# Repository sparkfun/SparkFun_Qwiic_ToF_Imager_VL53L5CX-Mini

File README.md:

SparkFun Qwiic ToF Imager with VL53L5CX
========================================

[*SparkFun Qwiic Mini ToF Imager - VL53L5CX (SEN-19013)*](https://www.sparkfun.com/products/19013)

The SparkFun Qwiic Mini ToF Imager is a state of the art, 64 pixel Time-of-Flight (ToF) 4 meter ranging sensor built around the VL53L5CX from ST. This _Mini_ version has a footprint that is half the size (0.5 in x 1 in) of our standard [Qwiic VL53L5CX](https://www.sparkfun.com/products/18642). Additionally, we moved the Qwiic connectors to the back of the board in a vertical orientation. These design changes favor mounting applications where the VL53L5CX sensor faces outward from an enclosure or chassis, and keeps your Qwiic cables cleanly tucked away.  

This chip integrates a SPAD array, physical infrared filters, and diffractive optical elements (DOE) to achieve the best ranging performance in various ambient lighting conditions with a range of cover glass materials. Utilizing our handy Qwiic system, no soldering is required to connect it to the rest of your system. However, we still have broken out **some** 0.1"-spaced pins in case you prefer to use a breadboard.

Multizone distance measurements up to 4000mm are possible across all 64 zones with a wide 63° diagonal field-of-view which can be read up to 15Hz. Thanks to ST Histogram patented algorithms, the VL53L5CX is able to detect different objects within the FoV. The Histogram also provides immunity to cover glass crosstalk beyond 60 cm.

Ideal for 3D room mapping, obstacle detection for robotics, gesture recognition, IoT, laser-assisted autofocus, and AR/VR enhancement, the Qwiic connector on this sensor makes integration easy. 

SparkFun labored with love to create this code. Feel like supporting open source hardware? 
Buy a [breakout board](https://www.sparkfun.com/products/14722) from SparkFun!

Repository Contents
-------------------

* **/Documents** - Datasheet and User Manual
* **/Hardware** - Eagle design files (.brd, .sch)

Documentation
--------------
* **[Arduino Library](https://github.com/sparkfun/SparkFun_VL53L5CX_Arduino_Library)** - Library for reading distance in millimeters, signal rate, status, etc.
* **[Hookup Guide](https://learn.sparkfun.com/tutorials/qwiic-tof-imager---vl53l5cx-hookup-guide)** - Hookup guide for the Qwiic ToF Imager VL53L5CX

License Information
-------------------

This product is _**open source**_! 

Please review the LICENSE.md file for license information. 

If you have any questions or concerns on licensing, please contact techsupport@sparkfun.com.

Please use, reuse, and modify these files as you see fit. Please maintain attribution to SparkFun Electronics and release any derivative under the same license.

Distributed as-is; no warranty is given.

- Your friends at SparkFun.

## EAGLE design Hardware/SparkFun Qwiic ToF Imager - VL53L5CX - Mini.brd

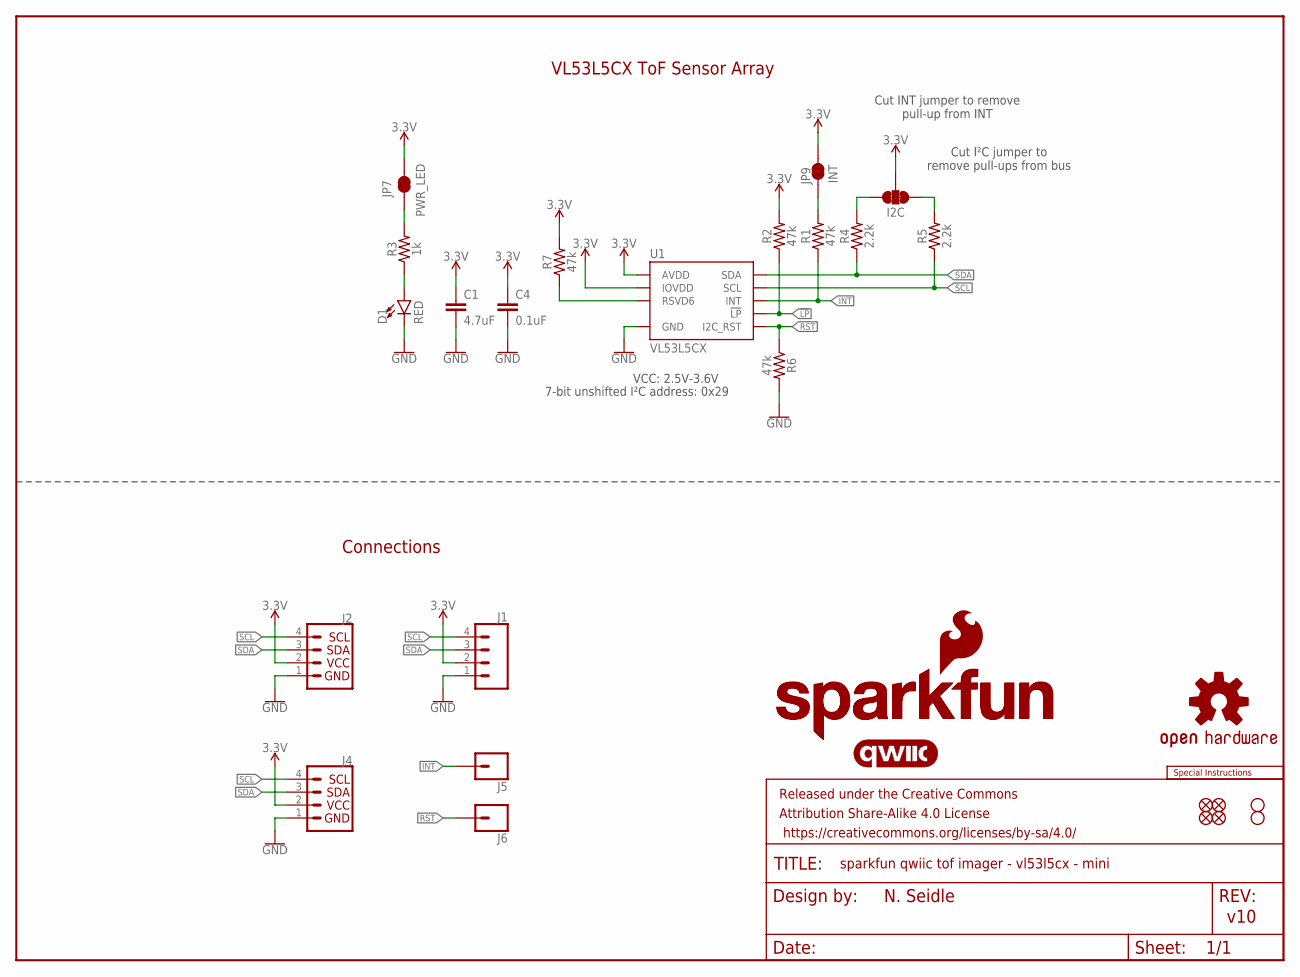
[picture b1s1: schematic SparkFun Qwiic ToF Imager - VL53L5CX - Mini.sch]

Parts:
C1: 4.7uF; 0402-TIGHT
C4: 0.1uF; 0402-TIGHT
D1: RED; LED-0603
FRAME1: FRAME-LETTER; CREATIVE_COMMONS
I2C: JUMPER-SMT_3_2-NC_TRACE_SILK; SMT-JUMPER_3_2-NC_TRACE_SILK
J1: CONN_041X04_NO_SILK; 1X04_NO_SILK
J2, J4: Vertical Qwiic Connector; JST04_1MM_VERT
J5, J6: CONN_01PTH_NO_SILK_YES_STOP; 1X01_NO_SILK
JP1, JP2, JP5, JP6: FIDUCIALUFIDUCIAL; FIDUCIAL-MICRO
JP7: PWR_LED; SMT-JUMPER_2_NC_TRACE_SILK
JP9: INT; SMT-JUMPER_2_NC_TRACE_SILK
JP10, JP11: STAND-OFF
LOGO1: SFE_LOGO_NAME_FLAME8_MM; SFE_LOGO_NAME_FLAME_8MM
LOGO2: OSHW-LOGONO_SILK; DUMMY
LOGO3: QWIIC_LOGO_CONNECTOR; QWIIC_5.5MM
LOGO4: SFE_LOGO_NAME6_MM; SFE_LOGO_NAME_6MM
LOGO5: SPECIAL_INSTRUCTIONS-ORDERING; ORDERING_INSTRUCTIONS
R1, R2, R6, R7: 47k; 0402-TIGHT
R3: 1k; 0402-TIGHT
R4, R5: 2.2k; 0402-TIGHT
U1: VL53L5CX

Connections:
3.3V: C1.1, C4.1, I2C.2, J1.2, J2.2, J4.2, JP7.2, JP9.2, R2.2, R7.2, U1.A4 (IOVDD), U1.B1 (AVDD), U1.B7 (AVDD)
!LP: R2.1, U1.A5 (!LP)
GND: C1.2, C4.2, D1.C, J1.1, J2.1, J4.1, R6.2, U1.A2 (GND), U1.A6 (GND), U1.A7 (GND), U1.B4 (GND), U1.C1 (GND), U1.C6 (GND), U1.C7 (GND)
INT: J5.1, R1.1, U1.A3 (INT)
unnamed: I2C.1, R5.2
unnamed: I2C.3, R4.2
unnamed: D1.A, R3.1
unnamed: JP9.1, R1.2
unnamed: JP7.1, R3.2
unnamed: R7.1, U1.C2 (RSVD6)
RST: J6.1, R6.1, U1.A1 (I2C_RST)
SCL: J1.4, J2.4, J4.4, R5.1, U1.C4 (SCL)
SDA: J1.3, J2.3, J4.3, R4.1, U1.C3 (SDA)

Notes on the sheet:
N. Seidle
v10
7-bit unshifted I²C address: 0x29
Cut I²C jumper to remove pull-ups from bus
Cut INT jumper to remove pull-up from INT
VCC: 2.5V-3.6V
VL53L5CX ToF Sensor Array
Connections

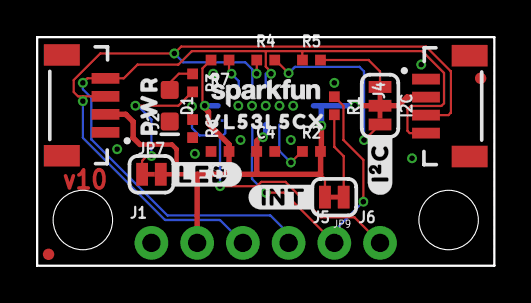
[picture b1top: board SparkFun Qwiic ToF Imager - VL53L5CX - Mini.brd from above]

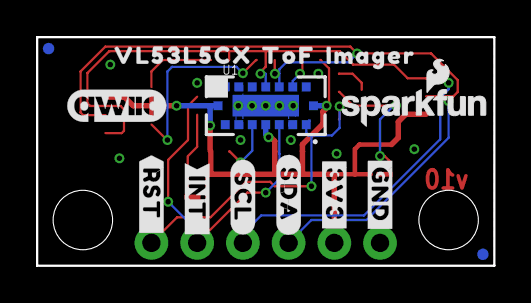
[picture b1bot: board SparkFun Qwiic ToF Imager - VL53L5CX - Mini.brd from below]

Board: 2 copper layers, 25.4 x 12.7 mm, 45 parts (14 on the bottom side), 13 nets.

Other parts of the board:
U$1: VL53L5CX_0
U$2: #LED#0
U$3: #3V3#13
U$4: PWR12
U$5: #INT#0
U$8: #INT_#0
U$9: #RST_#1
U$16: #I�C#0
U$19: VL53L5CX0
U$20: TOF1
U$22: IMAGER2
U$24: #SCL#1
U$25: #SDA#0
U$30: #GND#62130

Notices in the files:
parts and their libraries:
SparkFun-Resistors: Licensing: Creative Commons ShareAlike 4.0 International - https://creativecommons.org/licenses/by-sa/4.0
SparkFun-Aesthetics: Released under the Creative Commons Attribution Share-Alike 4.0 License
SparkFun-Aesthetics: https://creativecommons.org/licenses/by-sa/4.0
